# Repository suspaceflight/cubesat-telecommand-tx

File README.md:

# cubesat-telecommand-tx
WIP Telecommand Transmitter for the UoS3 Cubesat

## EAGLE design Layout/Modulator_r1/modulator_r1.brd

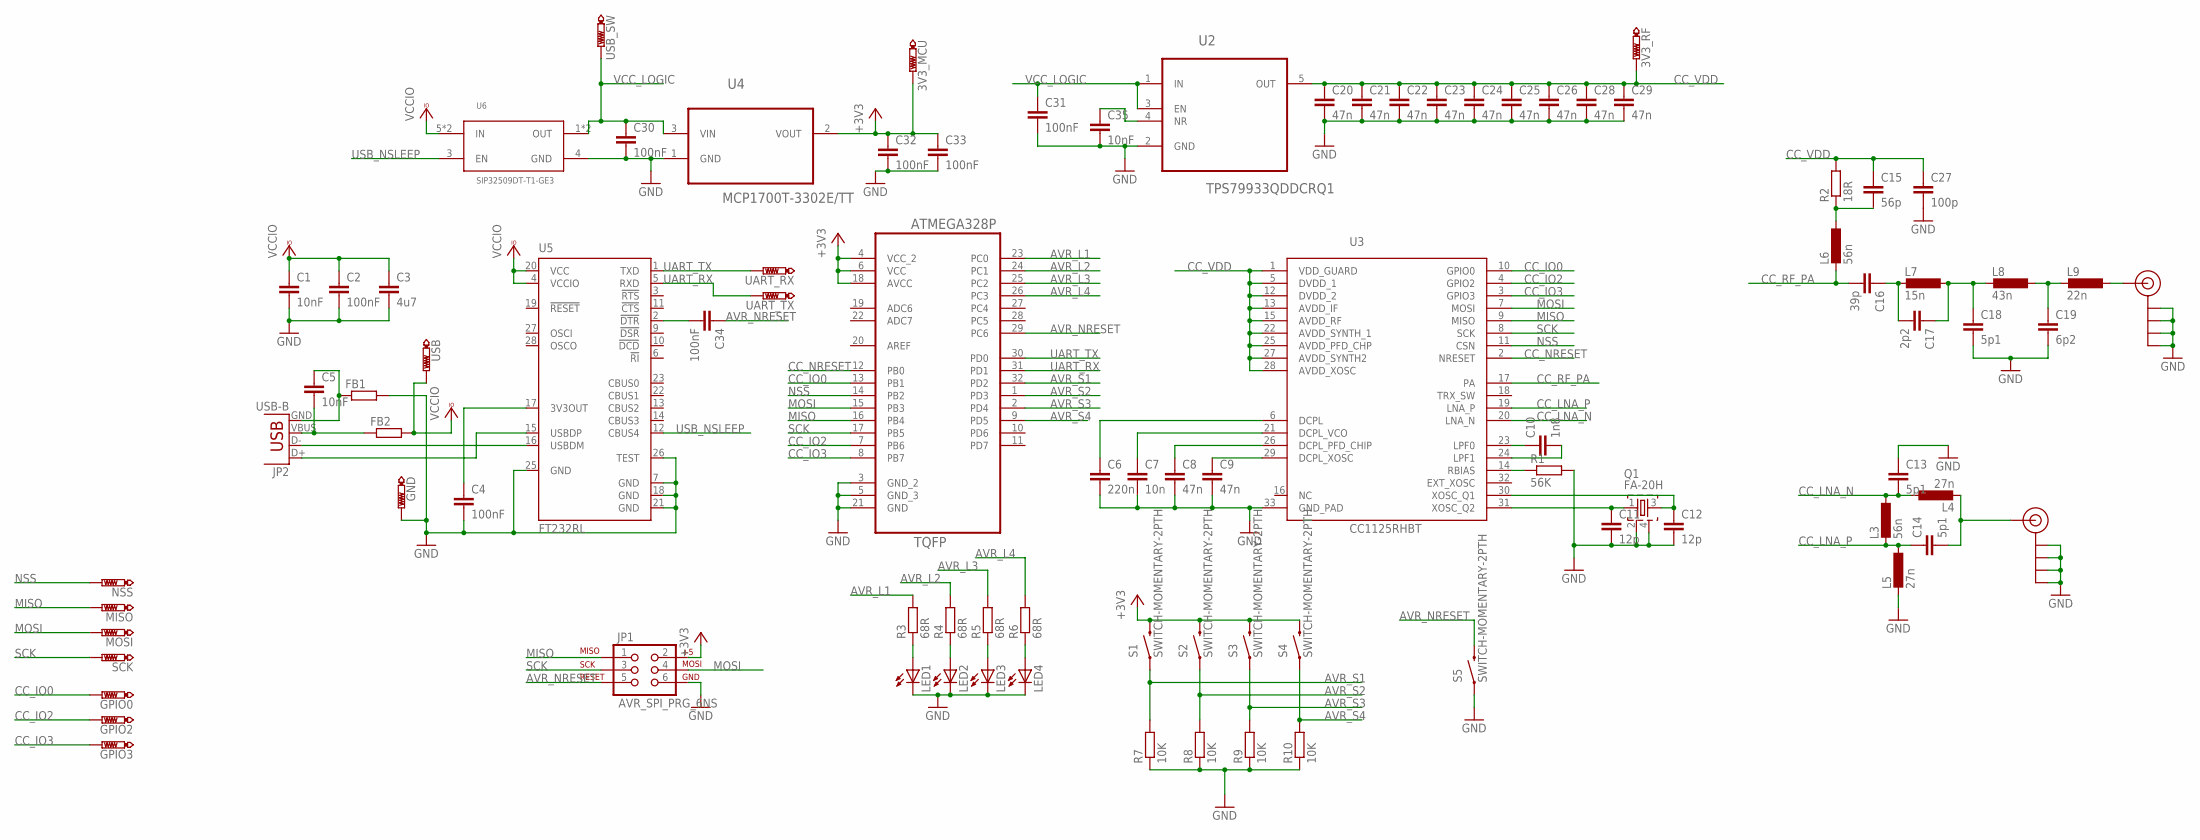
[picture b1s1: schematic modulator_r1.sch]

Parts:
3V3_MCU, 3V3_RF: PTR1B2,54; B2,54
C1, C5, C35: 10nF; C0603
C2, C4, C30, C31, C32, C33, C34: 100nF; C0603
C3: 4u7; C0603
C6: 220n; C0402
C7: 10n; C0402
C8, C9, C20, C21, C22, C23, C24, C25, C26, C28, C29: 47n; C0402
C10: 1n8; C0402
C11, C12: 12p; C0402
C13, C14, C18: 5p1; C0402
C15: 56p; C0402
C16: 39p; C0402
C17: 2p2; C0402
C19: 6p2; C0402
C27: 100p; C0402
FB1, FB2: R-EU_R0603; R0603
GND: PTR1B2,54; B2,54
GPIO0, GPIO2, GPIO3: PTR1B1,27; B1,27
J$1, J$2: SMA_EDGE; SMA-EDGE
JP1: AVR_SPI_PRG_6NS; 2X3-NS
JP2: USB-B; USB-B-PTH
L3, L6: 56n; R0402
L4, L5: 27n; R0402
L7: 15n; R0402
L8: 43n; R0402
L9: 22n; R0402
LED1, LED2, LED3, LED4: LEDCHIPLED_1206; CHIPLED_1206
MISO: PTR1B1,27; B1,27
MOSI: PTR1B1,27; B1,27
NSS: PTR1B1,27; B1,27
Q1: FA-20H
R1: 56K; R0402
R2: 18R; R0402
R3, R4, R5, R6: 68R; R0603
R7, R8, R9, R10: 10K; R0603
S1, S2, S3, S4, S5: SWITCH-MOMENTARY-2PTH; TACTILE-PTH
SCK: PTR1B1,27; B1,27
U1: ATMEGA328P-AU; QFP80P900X900X120-32N
U2: TPS79933QDDCRQ1; SOT95P280X110-5N
U3: CC1125RHBT; QFN50P500X500X100-32N
U4: MCP1700T-3302E/TT; SOT95P237X112-3N
U5: FT232RL; SSOP28
U6: SIP32509DT-T1-GE3; SOT23-6
UART_RX: PTR1B1,27; B1,27
UART_TX: PTR1B1,27; B1,27
USB: PTR1B2,54; B2,54
USB_SW: PTR1B2,54; B2,54

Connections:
+3V3: 3V3_MCU.TP, C32.1, C33.1, JP1.2, S1.3 (2), S2.3 (2), S3.3 (2), S4.3 (2), U1.4 (VCC_2), U1.6 (VCC), U1.18 (AVCC), U4.2 (VOUT)
AVR_L1: R3.2, U1.23 (PC0)
AVR_L2: R4.2, U1.24 (PC1)
AVR_L3: R5.2, U1.25 (PC2)
AVR_L4: R6.2, U1.26 (PC3)
AVR_NRESET: C34.1, JP1.5, S5.3 (2), U1.29 (PC6)
AVR_S1: R7.2, S1.1, U1.32 (PD2)
AVR_S2: R8.2, S2.1, U1.1 (PD3)
AVR_S3: R9.2, S3.1, U1.2 (PD4)
AVR_S4: R10.2, S4.1, U1.9 (PD5)
CC_IO0: GPIO0.TP, U1.13 (PB1), U3.10 (GPIO0)
CC_IO2: GPIO2.TP, U1.7 (PB6), U3.4 (GPIO2)
CC_IO3: GPIO3.TP, U1.8 (PB7), U3.3 (GPIO3)
CC_LNA_N: C13.2, L3.1, L4.1, U3.20 (LNA_N)
CC_LNA_P: C14.1, L3.2, L5.1, U3.19 (LNA_P)
CC_NRESET: U1.12 (PB0), U3.2 (NRESET)
CC_RF_PA: C16.2, L6.2, U3.17 (PA)
CC_VDD: 3V3_RF.TP, C15.1, C20.1, C21.1, C22.1, C23.1, C24.1, C25.1, C26.1, C27.1, C28.1, C29.1, R2.2, U2.5 (OUT), U3.1 (VDD_GUARD), U3.5 (DVDD_1), U3.12 (DVDD_2), U3.13 (AVDD_IF), U3.15 (AVDD_RF), U3.22 (AVDD_SYNTH_1), U3.25 (AVDD_PFD_CHP), U3.27 (AVDD_SYNTH2), U3.28 (AVDD_XOSC)
GND: C1.2, C2.2, C3.2, C4.2, C6.2, C7.2, C8.2, C9.2, C11.2, C12.2, C13.1, C18.2, C19.2, C20.2, C21.2, C22.2, C23.2, C24.2, C25.2, C26.2, C27.2, C28.2, C29.2, C30.2, C31.2, C32.2, C33.2, C35.2, FB1.2, GND.TP, J$1.GND@0 (GND), J$1.GND@1 (GND), J$1.GND@2 (GND), J$1.GND@3 (GND), J$2.GND@0 (GND), J$2.GND@1 (GND), J$2.GND@2 (GND), J$2.GND@3 (GND), JP1.6, L5.2, LED1.C, LED2.C, LED3.C, LED4.C, Q1.2, Q1.4, R1.2, R7.1, R8.1, R9.1, R10.1, S5.1, U1.3 (GND_2), U1.5 (GND_3), U1.21 (GND), U2.2 (GND), U3.33 (GND_PAD), U4.1 (GND), U5.7 (GND), U5.18 (GND), U5.21 (GND), U5.25 (GND), U5.26 (TEST), U6.4 (GND)
MISO: JP1.1, MISO.TP, U1.16 (PB4), U3.9 (MISO)
MOSI: JP1.4, MOSI.TP, U1.15 (PB3), U3.7 (MOSI)
unnamed: JP2.D-, U5.16 (USBDM)
unnamed: JP2.D+, U5.15 (USBDP)
unnamed: C5.1, FB1.1, JP2.GND
unnamed: C5.2, FB2.1, JP2.VBUS
unnamed: C4.1, U5.17 (3V3OUT)
unnamed: J$2.SIG (SIGNAL), L9.1
unnamed: R1.1, U3.14 (RBIAS)
unnamed: C9.1, U3.29 (DCPL_XOSC)
unnamed: C8.1, U3.26 (DCPL_PFD_CHIP)
unnamed: C7.1, U3.21 (DCPL_VCO)
unnamed: C6.1, U3.6 (DCPL)
unnamed: C10.2, U3.24 (LPF1)
unnamed: C10.1, U3.23 (LPF0)
unnamed: C11.1, Q1.1, U3.31 (XOSC_Q2)
unnamed: C19.1, L8.1, L9.2
unnamed: C12.1, Q1.3, U3.30 (XOSC_Q1)
unnamed: C14.2, J$1.SIG (SIGNAL), L4.2
unnamed: C17.1, C18.1, L7.1, L8.2
unnamed: C16.1, C17.2, L7.2
unnamed: C34.2, U5.2 (!DTR)
unnamed: C15.2, L6.1, R2.1
unnamed: LED1.A, R3.1
unnamed: LED2.A, R4.1
unnamed: LED3.A, R5.1
unnamed: LED4.A, R6.1
unnamed: C35.1, U2.4 (NR)
NSS: NSS.TP, U1.14 (PB2), U3.11 (CSN)
SCK: JP1.3, SCK.TP, U1.17 (PB5), U3.8 (SCK)
UART_RX: U1.31 (PD1), U5.5 (RXD), UART_TX.TP
UART_TX: U1.30 (PD0), U5.1 (TXD), UART_RX.TP
USB_NSLEEP: U5.12 (CBUS4), U6.3 (EN)
VCCIO: C1.1, C2.1, C3.1, FB2.2, U5.4 (VCCIO), U5.20 (VCC), U6.5 (IN), U6.6 (IN), USB.TP
VCC_LOGIC: C30.1, C31.1, U2.1 (IN), U2.3 (EN), U4.3 (VIN), U6.1 (OUT), U6.2 (OUT), USB_SW.TP

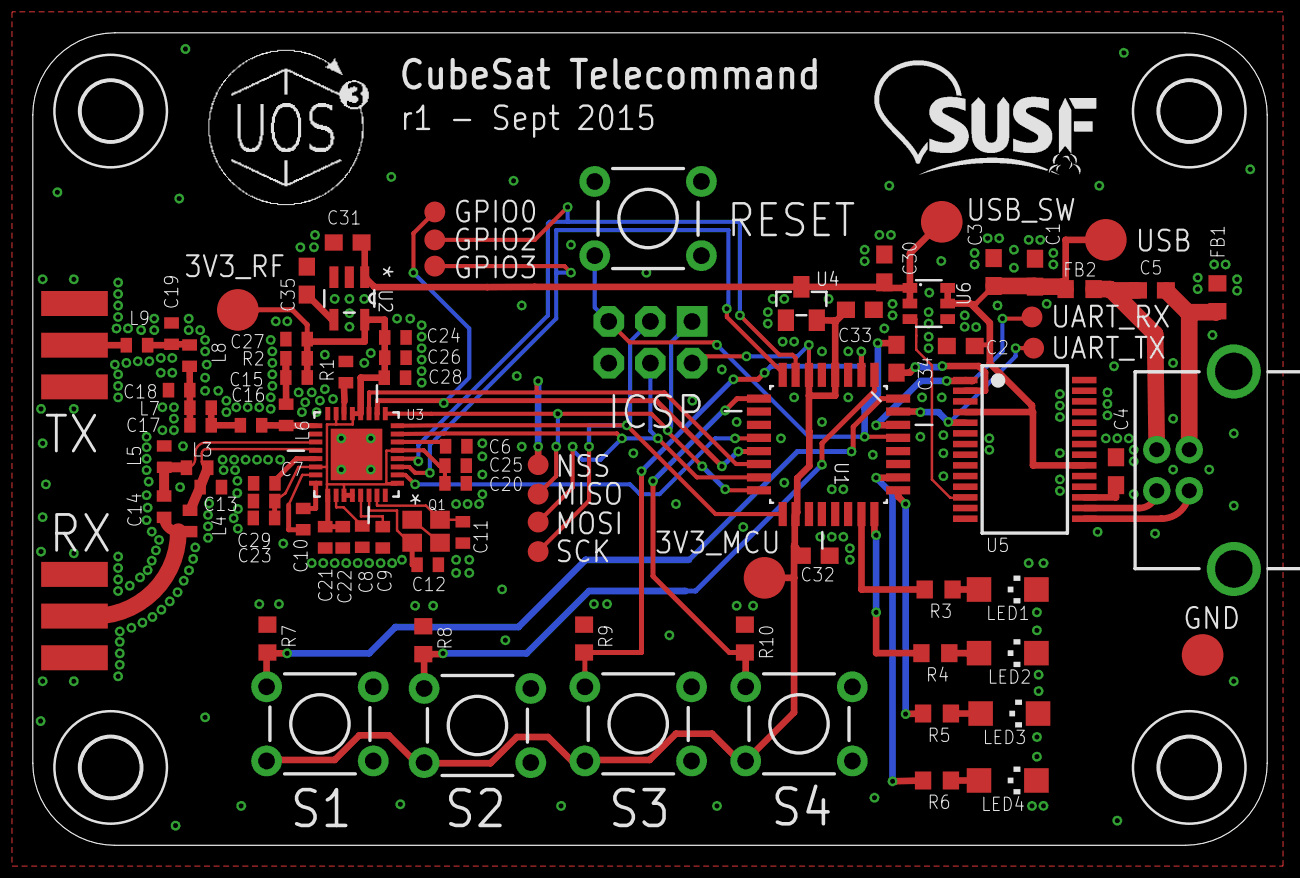
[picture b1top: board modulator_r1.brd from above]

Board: 2 copper layers, 75.2 x 49.5 mm, 93 parts (0 on the bottom side), 54 nets.

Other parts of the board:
U$1: SUSF-XSM
U$2, U$3, U$4, U$5: 3,6

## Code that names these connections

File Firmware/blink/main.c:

#define F_CPU 1000000UL

#include <avr/io.h>
#include <util/delay.h>

void led_on(uint8_t led_num);
void led_off(uint8_t led_num);

int main(void)
{
    DDRC |= _BV(DDC0) | _BV(DDC1) | _BV(DDC2) | _BV(DDC3); 
    
    while(1) 
    {
        led_on(1);
        led_off(3);
        _delay_ms(100);
        led_on(2);
        led_off(4);
        _delay_ms(100);
        led_on(3);
        led_off(1);
        _delay_ms(100);
        led_on(4);
        led_off(2);
        _delay_ms(100);
    }
}

void led_on(uint8_t led_num)
{
    switch(led_num)
    {
        case 1:
            PORTC |= _BV(PC0);
            break;
        case 2:
            PORTC |= _BV(PC1);
            break;
        case 3:
            PORTC |= _BV(PC2);
            break;
        case 4:
            PORTC |= _BV(PC3);
            break;
    }
}

void led_off(uint8_t led_num)
{
    switch(led_num)
    {
        case 1:
            PORTC &= ~(_BV(PC0));
            break;
        case 2:
            PORTC &= ~(_BV(PC1));
            break;
        case 3:
            PORTC &= ~(_BV(PC2));
            break;
        case 4:
            PORTC &= ~(_BV(PC3));
            break;
    }
}

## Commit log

2015-05-09 Add gitignores.
2015-05-09 Add Layout library submodules.
2015-05-09 Start schematic.
2015-06-01 Add element14 TI lbr.
2015-06-04 Add hackvana DRU.
2015-06-04 Add CC1125 to TI lbr.
2015-06-04 Progress on board.
2015-06-07 Layout progress.
2015-06-10 Add USB power switch, start routing.
2015-07-03 Layout Modulator_r1
2015-07-27 Add switches, general layout churn.
2015-09-28 Progress.
2015-09-29 Connected CC_Reset and GPIO0.
2015-09-29 Clear up DRC errors.
2015-09-29 Connect GPIO2/3.
2015-09-29 Add test pads.
2015-09-29 Add cam file.
2015-09-29 Tweak labels.
2015-09-30 Add UoS3 and SUSF logos. Closes #7.
2015-09-30 Add DTR coupling to reset. Closes #9.
2015-09-30 Tweak silkscreen.
2015-09-30 Fatten some traces. Probably closes #8.
2015-09-30 Redo RX layout to better match TI Reference.
2015-09-30 Complete LDO circuit.
2015-09-30 Actually line up mounting holes.
2015-10-01 Change tnames to vector. Closes #10.
2015-10-27 Add test fw.
2015-10-29 Add Assembly and BOM.

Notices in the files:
parts and their libraries:
SparkFun-Connectors: Licensing: Creative Commons ShareAlike 4.0 International - https://creativecommons.org/licenses/by-sa/4.0
